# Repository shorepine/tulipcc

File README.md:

# Tulip Creative Computer and AMYboard - portable programmable devices for music, graphics, code and writing

Welcome to the Tulip Creative Computer (Tulip CC) and AMYboard!
 
Tulip is a low power and affordable self-contained portable computer, with a touchscreen display and sound. It's fully programmable - you write code to define your music, games or anything else you can think of. It boots instantaneously into a Python prompt with a lot of built in support for music synthesis, fast graphics and text, hardware MIDI, network access and external sensors. Dive right into making something without distractions or complications. 

The entire system is dedicated to your code, the display and sound, running in real time, on specialized hardware. The hardware and software are fully open source and anyone can [buy one](https://tulip.computer/) or [build one](docs/tulip_build.md). You can use Tulip to make music, code, art, games, or just write. 

[AMYboard](https://amyboard.com) is a headless (no screen) version of Tulip with more audio capability - audio input, modular 10hp and 10vpp audio, S/PDIF digital audio, CV jacks, SD card. It's based on the Tulip code but focused on music synthesis. 

You can now even [run Tulip on the web](https://tulip.computer/run) and [AMYboard on the web](https://amyboard.com/editor) and share your creations with anyone!

Tulip and AMYboard are powered by [MicroPython](https://micropython.org), [AMY](https://github.com/shorepine/amy), and [LVGL](https://lvgl.io). The Tulip hardware runs on the ESP32-S3 chip using the [ESP-IDF](https://github.com/espressif/esp-idf).

 * [**Get a Tulip** from our friends at Makerfabs for only US$59](https://tulip.computer)
 * [**Get an AMYboard** from our friends at Makerfabs for only $29.90](https://amyboard.com)
 * [Just got a Tulip CC? **Check out our getting started guide!**](docs/getting_started.md)
 * [Just got an AMYboard? **Check out our getting started guide!**](docs/amyboard/README.md)
 * [Want to make music with your Tulip? **See our music tutorial**](docs/music.md)
 * [See the full **Tulip API**](docs/tulip_api.md)
 * [**Try out Tulip on the web!**](https://tulip.computer/run/)

 [ **Chat about Tulip on our Discord!**](https://discord.gg/TzBFkUb8pG)

**Check out this video!**

[![Tulip, a musical computer based on Micropython
](https://i.ytimg.com/vi/1lYFjQp7Xrw/maxresdefault.jpg)](https://www.youtube.com/watch?v=1lYFjQp7Xrw "Tulip, a musical computer based on Micropython")

You can use Tulip one of three ways:
 * Tulip is available both as an [off the shelf or DIY hardware project (Tulip CC)](https://tulip.computer/)
 * [Tulip runs on the web](https://tulip.computer/run) with (almost) all the same features. 
 * Tulip can also run as a native app for Mac or Linux (or WSL in Windows) as [Tulip Desktop](docs/tulip_desktop.md)

If you're nervous about getting or building the hardware, [try it out on the web!](https://tulip.computer/run)

The hardware Tulip CC supports:

- 8.5MB of RAM - 2MB is available to MicroPython, and 1.5MB is available for OS memory. The rest is used for the graphics framebuffers (which you can use as storage) and the firmware cache. 
- 32MB flash storage, as a filesystem accesible in Python (24MB left over after OS in ROM)
- An [AMY](https://github.com/shorepine/amy) stereo 120-voice synthesizer engine running locally, or as a wireless controller for an [Alles](https://github.com/shorepine/alles) mesh. Tulip's synth supports additive and subtractive oscillators, an excellent FM synthesis engine, samplers, karplus-strong, high quality analog style filters, a sequencer, and much more. We ship Tulip with a drum machine, voices / patch app, and Juno-6 editor.
- Text frame buffer layer, 128 x 50, with ANSI support for 256 colors, inverse, bold, underline, background color
- Up to 32 sprites on screen, drawn per scanline, with collision detection, from a total of 32KB of bitmap memory (1 byte per pixel)
- A 1024 (+128 overscan) by 600 (+100 overscan) background frame buffer to draw arbitrary bitmaps to, or use as RAM, and which can scroll horizontally / vertically
- WiFi, access http via Python requests or TCP / UDP sockets 
- Adjustable display clock and resolution, defaults to 30 FPS at 1024x600.
- 256 colors
- Can load PNGs from disk to set sprites or background, or generate bitmap data from code
- Built in code and text editor
- Built in BBS chat room and file transfer area called **TULIP ~ WORLD**
- USB keyboard, MIDI and mouse support, including hubs 
- Capactive multi-touch support (mouse on Tulip Desktop and Tulip Web)
- MIDI input and output
- I2C / Grove / Mabee connector, compatible with [many I2C devices like joysticks, keyboard, GPIO, DACs, ADCs, hubs](docs/tulip_api.md#i2c--grove--mabee)
- 575mA power usage @ 5V including display, at medium display brightness, can last for hours on LiPo, 18650s, or USB battery pack 

I've been working on Tulip on and off for years over many hardware iterations and hope that someone out there finds it as fun as I have, either making things with Tulip or working on Tulip itself. I'd love feedback, your own Tulip experiments or pull requests to improve the system.

 * [**Any issues with your Tulip CC? Here's our troubleshooting guide**](docs/troubleshooting.md)
 * [**Learn about our roadmap and find out what we're working on next**](https://github.com/orgs/shorepine/projects/1)
 * [**Build your own Tulip**](docs/tulip_build.md)
 * **[You can read more about the "why" or "how" of Tulip on my website!](https://notes.variogram.com/2024/07/30/tulip-available/)** 

## T-Deck Tulip CC

A **new** small option: get yourself a [T-Deck](https://www.aliexpress.us/item/3256805505920840.html?gatewayAdapt=glo2usa4itemAdapt) and install Tulip CC on it directly! [Check out our T-Deck page for more detail.](tulip/tdeck/README.md)

## Getting started

Once you've [bought a Tulip](https://tulip.computer), [opened Tulip Web](https://tulip.computer/run), [built a Tulip](docs/tulip_build.md) or [installed Tulip Desktop](docs/tulip_desktop.md), you'll see that Tulip boots right into a Python prompt and all interaction with the system happens there. You can make your own Python programs with Tulip's built in editor and execute them, or just experiment on the Tulip REPL prompt in real time.

[**See the full Tulip API**](docs/tulip_api.md) for more details on all the graphics, sound and input functions.

Below are a few getting started tips and small examples. The [full API](docs/tulip_api.md) page has more detail on everything you can do on a Tulip. [**See a more complete getting started page**](docs/getting_started.md) or [**a music making tutorial**](docs/music.md) as well!

```python
# Run a saved Python file. Control-C stops it
cd('ex') # The ex folder has a few examples and graphics in it
execfile("parallax.py")
# If you want to run a Tulip package (folder with other files in it)
run("game")
```

### The Tulip Editor

Tulip ships with a text editor, based on pico/nano. It supports syntax highlighting, search, save/save-as. 

```python
# Opens the Tulip editor to the given filename. 
edit("game.py")
```

### Input and user interface

Tulip supports USB keyboard and mice input as well as touch input. (On Tulip Desktop and Web, mouse clicks act as touch points.) It also comes with UI elements like buttons and sliders to use in your applications, and a way to run mulitple applications as once using callbacks. More in the [full API](docs/tulip_api.md).

```python
(x0, y0, x1, y1, x2, y2) = tulip.touch()
```

### Network

Tulip CC has the capability to connect to a Wi-Fi network, and Python's native requests library will work to access TCP and UDP. We ship a few convenience functions to grab data from URLs as well. More in the [full API](docs/tulip_api.md).

```python
# Join a wifi network (not needed on Tulip Desktop or Web)
tulip.wifi("ssid", "password")

# Get IP address or check if connected
ip_address = tulip.ip() # returns None if not connected

# Save the contents of a URL to disk (needs wifi)
bytes_read = tulip.url_save("https://url", "filename.ext")
```

### Music / sound

Tulip comes with the AMY synthesizer, a very full featured 120-oscillator synth that supports FM, PCM, additive synthesis, partial synthesis, filters, and much more. We also provide a useful "music computer" for scales, chords and progressions. More in the [full API](docs/tulip_api.md) and in the [music tutorial.](docs/music.md) Tulip's version of AMY comes with stereo sound, which you can set per oscillator with the `pan` parameter.

```python
amy.drums() # plays a test song
amy.send(volume=4) # change volume
amy.reset() # stops all music / sounds playing
```
https://user-images.githubusercontent.com/76612/215893940-658144b7-0c6f-42e2-9836-bd271597aab3.mov

### MIDI

Tulip supports MIDI in and out to connect to external music hardware. You can set up a Python callback to respond immediately to any incoming MIDI message. You can also send messages out to MIDI out. More in the [full API](docs/tulip_api.md) and [music tutorial](docs/music.md).

```python
m = tulip.midi_in() # returns bytes of the last MIDI message received
tulip.midi_out((144,60,127)) # sends a note on message
tulip.midi_out(bytes) # Can send bytes or list
```

### Graphics system

The Tulip GPU supports a scrolling background layer, hardware sprites, and a text layer. Much more in the [full API](docs/tulip_api.md).

```python
# Set or get a pixel on the BG
pal_idx = tulip.bg_pixel(x,y)

# Set the contents of a PNG file on the background.
tulip.bg_png(png_filename, x, y)

tulip.bg_scroll(line, x_offset, y_offset, x_speed, y_speed)
```

https://user-images.githubusercontent.com/76612/215895305-7b02ad27-b02a-429a-92ef-f13136e9f9d2.mov

Hardware sprites are supported. They draw over the background and text layer per scanline per frame:

```python
(w, h, bytes) = tulip.sprite_png("filename.png", mem_pos)

...

# Set a sprite x and y position
tulip.sprite_move(12, x, y)
```

https://user-images.githubusercontent.com/76612/215896311-fc0823aa-44bc-4305-85db-a6773db11a98.mov

### Tulip World

Still very much early days, but Tulip supports a native chat and file sharing BBS called **TULIP ~ WORLD** where you can hang out with other Tulip owners. You're able to pull down the latest messages and files and send messages and files yourself. More in the [full API](docs/tulip_api.md).

```python
import world
world.post_message("hello!!") # Sends a message to Tulip World. username required. will prompt if not set
world.upload(filename) # Uploads a file to Tulip World. username required
world.ls() # lists most recent unique filenames/usernames
```

## How to build, compile and help develop Tulip

 * [Get a Tulip!](https://tulip.computer)
 * [Build your own Tulip Creative Computer](docs/tulip_build.md) with FOUR different options.
 * [How to compile and flash Tulip hardware](docs/tulip_flashing.md)
 * [How to run or compile Tulip Desktop](docs/tulip_desktop.md)
 * [The full Tulip API](docs/tulip_api.md)
 * [File any code issues or pull requests!](https://github.com/shorepine/tulipcc/issues)

[ **Chat about Tulip on our Discord!**](https://discord.gg/TzBFkUb8pG)

Two important development guidelines if you'd like to help contribute!

 * Be nice and helpful and don't be afraid to ask questions! We're all doing this for fun and to learn. 
 * Any change or feature must be equivalent across Tulip Desktop and Tulip CC. There are of course limited exceptions to this rule, but please test on hardware before proposing a new feature / change. 

Have fun!

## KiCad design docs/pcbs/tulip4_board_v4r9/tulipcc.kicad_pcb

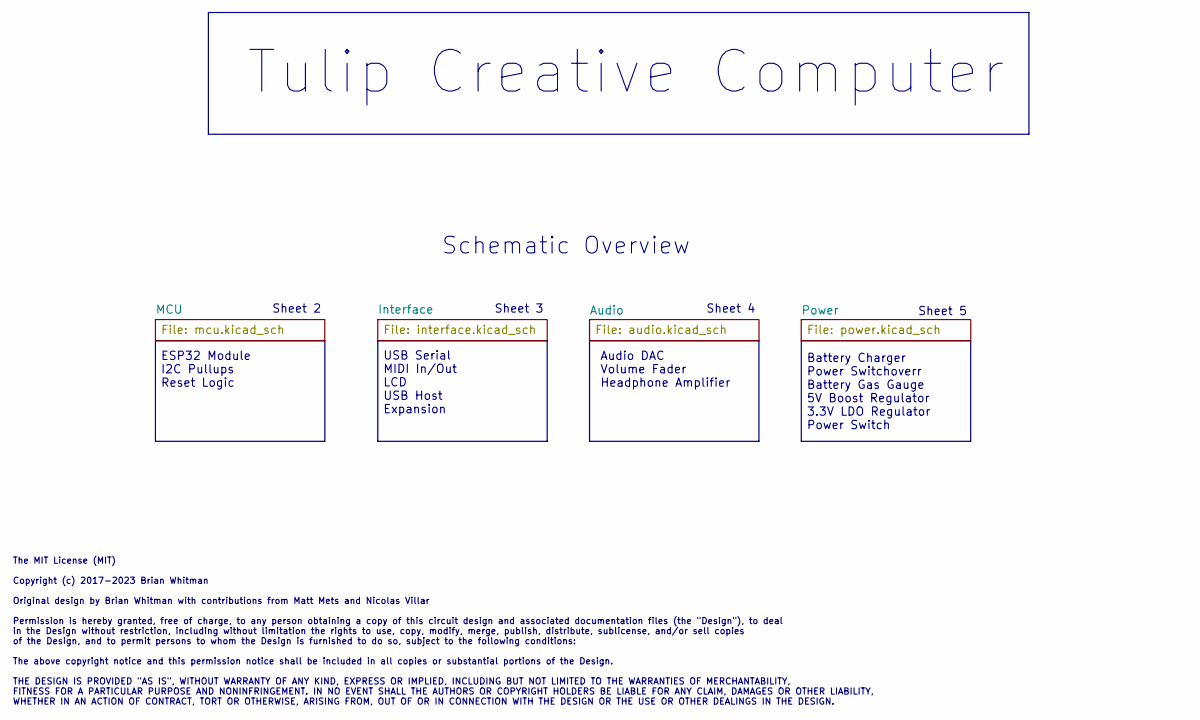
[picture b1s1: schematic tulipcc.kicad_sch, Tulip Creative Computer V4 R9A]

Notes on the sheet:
Schematic Overview
Sheet 2
Sheet 3
Battery Charger Power Switchoverr Battery Gas Gauge 5V Boost Regulator 3.3V LDO Regulator Power Switch
USB Serial MIDI In/Out LCD USB Host Expansion
Tulip Creative Computer
Sheet 4
Sheet 5
The MIT License (MIT) Copyright (c) 2017-2023 Brian Whitman Original design by Brian Whitman with contributions from Matt Mets and Nicolas Villar Permission is hereby granted, free of charge, to any person obtaining a copy of this circuit design and associated documentation files (the "Design"), to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
Audio DAC Volume Fader Headphone Amplifier
ESP32 Module I2C Pullups Reset Logic

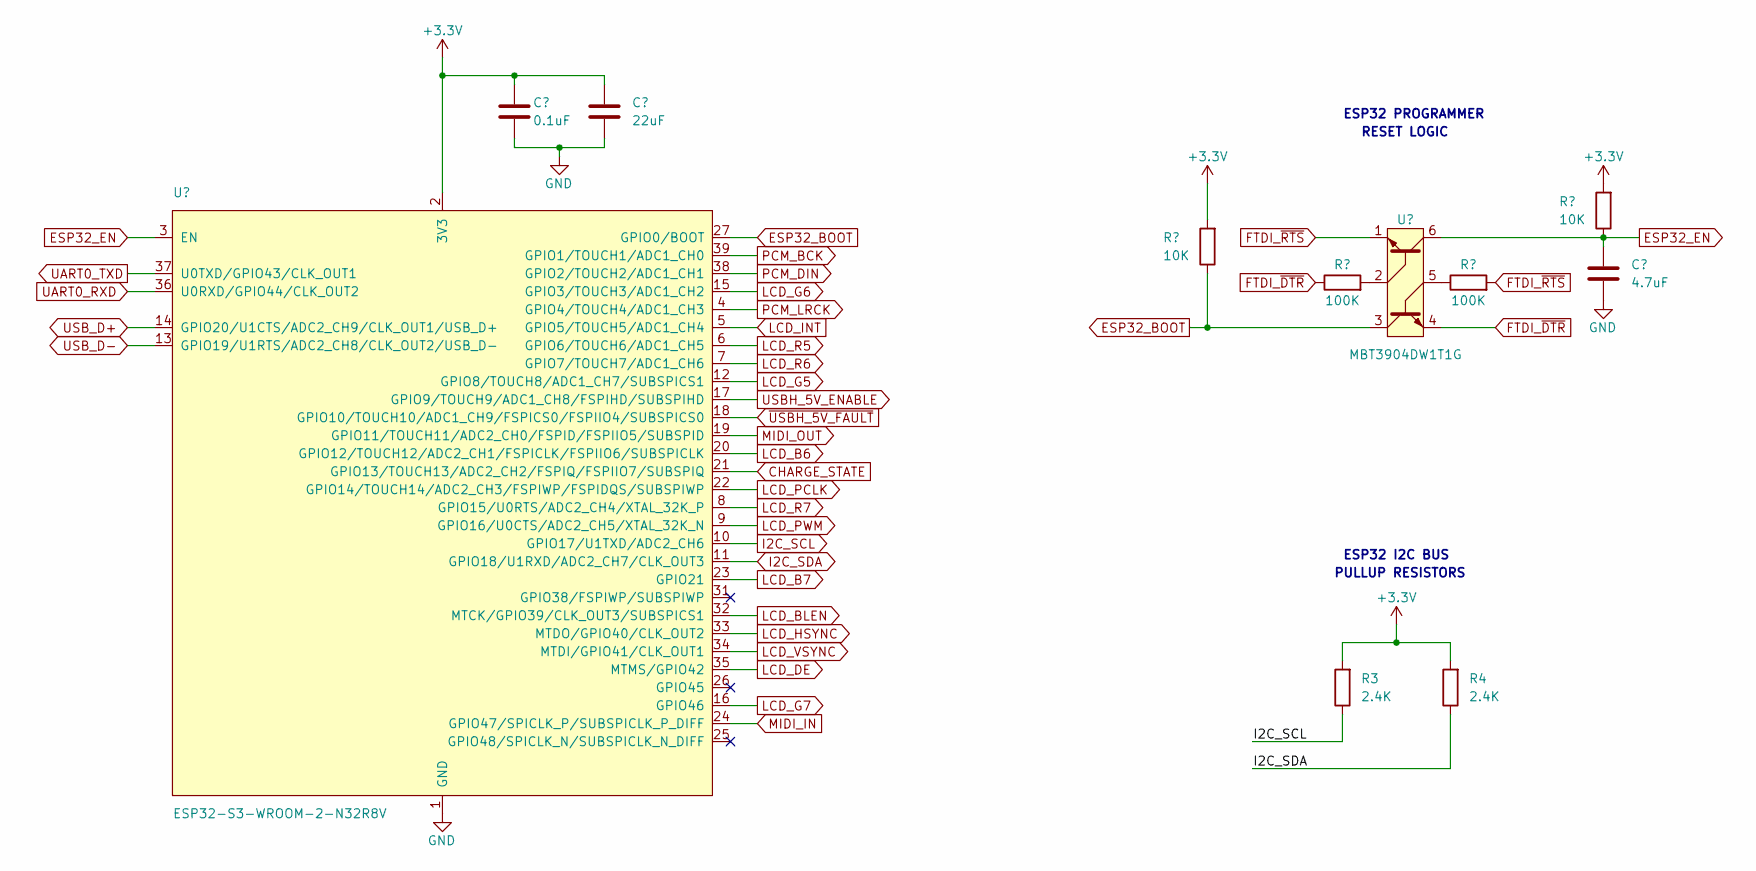
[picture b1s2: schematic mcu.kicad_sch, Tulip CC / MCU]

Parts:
C1: 0.1uF; C_0805_2012; Part # C0805C104K5RAC7411
C2: 22uF; C_1210_3225; Rating 16V; Part # C1210C226M4RAC7210
C3: 4.7uF; C_0805_2012; Part # C0805C475K3RACTU
R1, R2: 10K; R_0805_2012; Part # CR0805-FX-1002ELF
R3, R4: 2.4K; R_0805_2012; Part # CR0805-FX-2401ELF
R5, R6: 100K; R_0805_2012; Part # CR0805-FX-1003ELF
U1: ESP32-S3-WROOM-2-N32R8V; ESP32-S3-WROOM-2; Part # ESP32-S3-WROOM-2-N32R8V
U2: MBT3904DW1T1G; SOT-363_SC-70-6; Part # MBT3904DW1T1G

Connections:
+3.3V: C1.1, C2.2, R1.2, R2.2, R3.2, R4.2, U1.2 (3V3); also elsewhere on the board
CHARGE_STATE: U1.21 (GPIO13/TOUCH13/ADC2_CH2/FSPIQ/FSPIIO7/S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); also elsewhere on the board
ESP32_BOOT: R2.1, U1.27 (GPIO0/BOOT), U2.3
ESP32_EN: C3.1, R1.1, U1.3 (EN), U2.6
FTDI_~DTR: R5.1, U2.4; also elsewhere on the board
FTDI_~RTS: R6.2, U2.1; also elsewhere on the board
GND: C1.2, C2.1, C3.2, U1.1 (GND), U1.40 (GND), U1.41 (GND); also elsewhere on the board
I2C_SCL: R3.1, U1.10 (GPIO17/U1TXD/ADC2_CH6); also elsewhere on the board
I2C_SDA: R4.1, U1.11 (GPIO18/U1RXD/ADC2_CH7/CLK_OUT3); also elsewhere on the board
LCD_B6: U1.20 (GPIO12/TOUCH12/ADC2_CH1/FSPICLK/FSPIIO6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); also elsewhere on the board
LCD_B7: U1.23 (GPIO21); also elsewhere on the board
LCD_BLEN: U1.32 (MTCK/GPIO39/CLK_OUT3/SUBSPICS1); also elsewhere on the board
LCD_DE: U1.35 (MTMS/GPIO42); also elsewhere on the board
LCD_G5: U1.12 (GPIO8/TOUCH8/ADC1_CH7/SUBSPICS1); also elsewhere on the board
LCD_G6: U1.15 (GPIO3/TOUCH3/ADC1_CH2); also elsewhere on the board
LCD_G7: U1.16 (GPIO46); also elsewhere on the board
LCD_HSYNC: U1.33 (MTDO/GPIO40/CLK_OUT2); also elsewhere on the board
LCD_INT: U1.5 (GPIO5/TOUCH5/ADC1_CH4); also elsewhere on the board
LCD_PCLK: U1.22 (GPIO14/TOUCH14/ADC2_CH3/FSPIWP/FSPIDQS/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); also elsewhere on the board
LCD_PWM: U1.9 (GPIO16/U0CTS/ADC2_CH5/XTAL_32K_N); also elsewhere on the board
LCD_R5: U1.6 (GPIO6/TOUCH6/ADC1_CH5); also elsewhere on the board
LCD_R6: U1.7 (GPIO7/TOUCH7/ADC1_CH6); also elsewhere on the board
LCD_R7: U1.8 (GPIO15/U0RTS/ADC2_CH4/XTAL_32K_P); also elsewhere on the board
LCD_VSYNC: U1.34 (MTDI/GPIO41/CLK_OUT1); also elsewhere on the board
MIDI_IN: U1.24 (GPIO47/SPICLK_P/SUBSPICLK_P_DIFF); also elsewhere on the board
MIDI_OUT: U1.19 (GPIO11/TOUCH11/ADC2_CH0/FSPID/FSPIIO5/S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); also elsewhere on the board
unnamed: R5.2, U2.2
unnamed: R6.1, U2.5
PCM_BCK: U1.39 (GPIO1/TOUCH1/ADC1_CH0); also elsewhere on the board
PCM_DIN: U1.38 (GPIO2/TOUCH2/ADC1_CH1); also elsewhere on the board
PCM_LRCK: U1.4 (GPIO4/TOUCH4/ADC1_CH3); also elsewhere on the board
UART0_RXD: U1.36 (U0RXD/GPIO44/CLK_OUT2); also elsewhere on the board
UART0_TXD: U1.37 (U0TXD/GPIO43/CLK_OUT1); also elsewhere on the board
USBH_5V_ENABLE: U1.17 (GPIO9/TOUCH9/ADC1_CH8/FSPIHD/SUBSPIHD); also elsewhere on the board
USB_D+: U1.14 (GPIO20/U1CTS/ADC2_CH9/CLK_OUT1/USB_D+); also elsewhere on the board
USB_D-: U1.13 (GPIO19/U1RTS/ADC2_CH8/CLK_OUT2/USB_D-); also elsewhere on the board
~USBH_5V_FAULT: U1.18 (GPIO10/TOUCH10/ADC1_CH9/FSPICS0/FSPIIO4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); also elsewhere on the board

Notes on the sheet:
PULLUP RESISTORS
RESET LOGIC
ESP32 I2C BUS
ESP32 PROGRAMMER

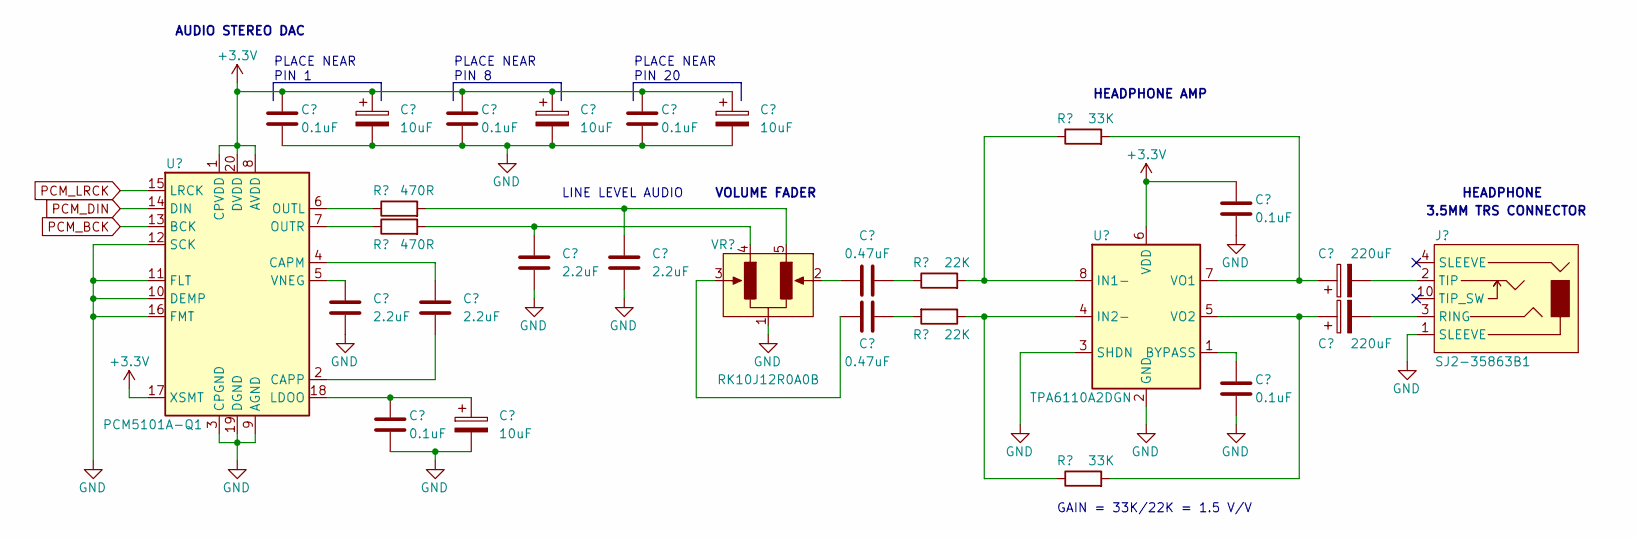
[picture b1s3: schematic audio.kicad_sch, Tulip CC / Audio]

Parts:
C11, C13, C15, C17, C26, C27: 0.1uF; C_0805_2012; Part # C0805C104K5RAC7411
C12, C14, C16, C28: 10uF; CAP_WE_865060340001; Rating 16V; Part # 865060340001
C18, C19, C22, C23: 2.2uF; C_0805_2012; Part # C0805C225K3RACTU
C20, C24: 0.47uF; C_0805_2012; Part # C0805C474K3RACTU
C21, C25: 220uF; CAP_WE_865060345007; Rating 16V; Part # 865060345007
J7: SJ2-35863B1; CON_CUI_SJ2-35863B1-SMT; Part # SJ2-35863B1-SMT-TR
R21, R26: 33K; R_0805_2012; Part # CR0805-FX-3002ELF
R22, R23: 470R; R_0805_2012; Part # CR0805-FX-4700ELF
R24, R25: 22K; R_0805_2012; Part # CR0805-FX-2202ELF
U8: PCM5101A-Q1; TSSOP-20_4.4x6.5mm_P0.65mm; Part # PCM5101AQPWRQ1
U9: TPA6110A2DGN; HVSSOP-8-1EP_3x3mm_P0.65mm_EP1.57x1.89mm; Part # TPA6110A2DGNR
VR1: RK10J12R0A0B; ALPS_RK10J12R0A0B; Part # RK10J12R0A0B

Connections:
+3.3V: C11.1, C12.1, C13.1, C14.1, C15.1, C16.1, C17.1, U8.1 (CPVDD), U8.8 (AVDD), U8.17 (XSMT), U8.20 (DVDD), U9.6 (VDD); also elsewhere on the board
GND: C11.2, C12.2, C13.2, C14.2, C15.2, C16.2, C17.2, C18.2, C19.2, C22.2, C26.2, C27.2, C28.2, J7.1 (SLEEVE), U8.3 (CPGND), U8.9 (AGND), U8.10 (DEMP), U8.11 (FLT), U8.12 (SCK), U8.16 (FMT), U8.19 (DGND), U9.2 (GND), U9.3 (SHDN), U9.9 (GND), VR1.1; also elsewhere on the board
unnamed: C18.1, R23.2, VR1.4
unnamed: C19.1, R22.2, VR1.5
unnamed: C20.1, R24.1
unnamed: C20.2, VR1.2
unnamed: C24.1, R25.2
unnamed: C24.2, VR1.3
unnamed: C25.2, J7.3 (RING)
unnamed: C21.2, J7.2 (TIP)
unnamed: C23.1, U8.4 (CAPM)
unnamed: C23.2, U8.2 (CAPP)
unnamed: C27.1, C28.1, U8.18 (LDOO)
unnamed: R22.1, U8.6 (OUTL)
unnamed: R23.1, U8.7 (OUTR)
unnamed: C22.1, U8.5 (VNEG)
unnamed: C26.1, U9.1 (BYPASS)
unnamed: R21.1, R24.2, U9.8 (IN1-)
unnamed: R25.1, R26.1, U9.4 (IN2-)
unnamed: C21.1, R21.2, U9.7 (VO1)
unnamed: C25.1, R26.2, U9.5 (VO2)
PCM_BCK: U8.13 (BCK); also elsewhere on the board
PCM_DIN: U8.14 (DIN); also elsewhere on the board
PCM_LRCK: U8.15 (LRCK); also elsewhere on the board

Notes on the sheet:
GAIN = 33K/22K = 1.5 V/V
3.5MM TRS CONNECTOR
HEADPHONE AMP
VOLUME FADER
PLACE NEAR PIN 20
PLACE NEAR PIN 1
HEADPHONE
PLACE NEAR PIN 8
LINE LEVEL AUDIO
AUDIO STEREO DAC

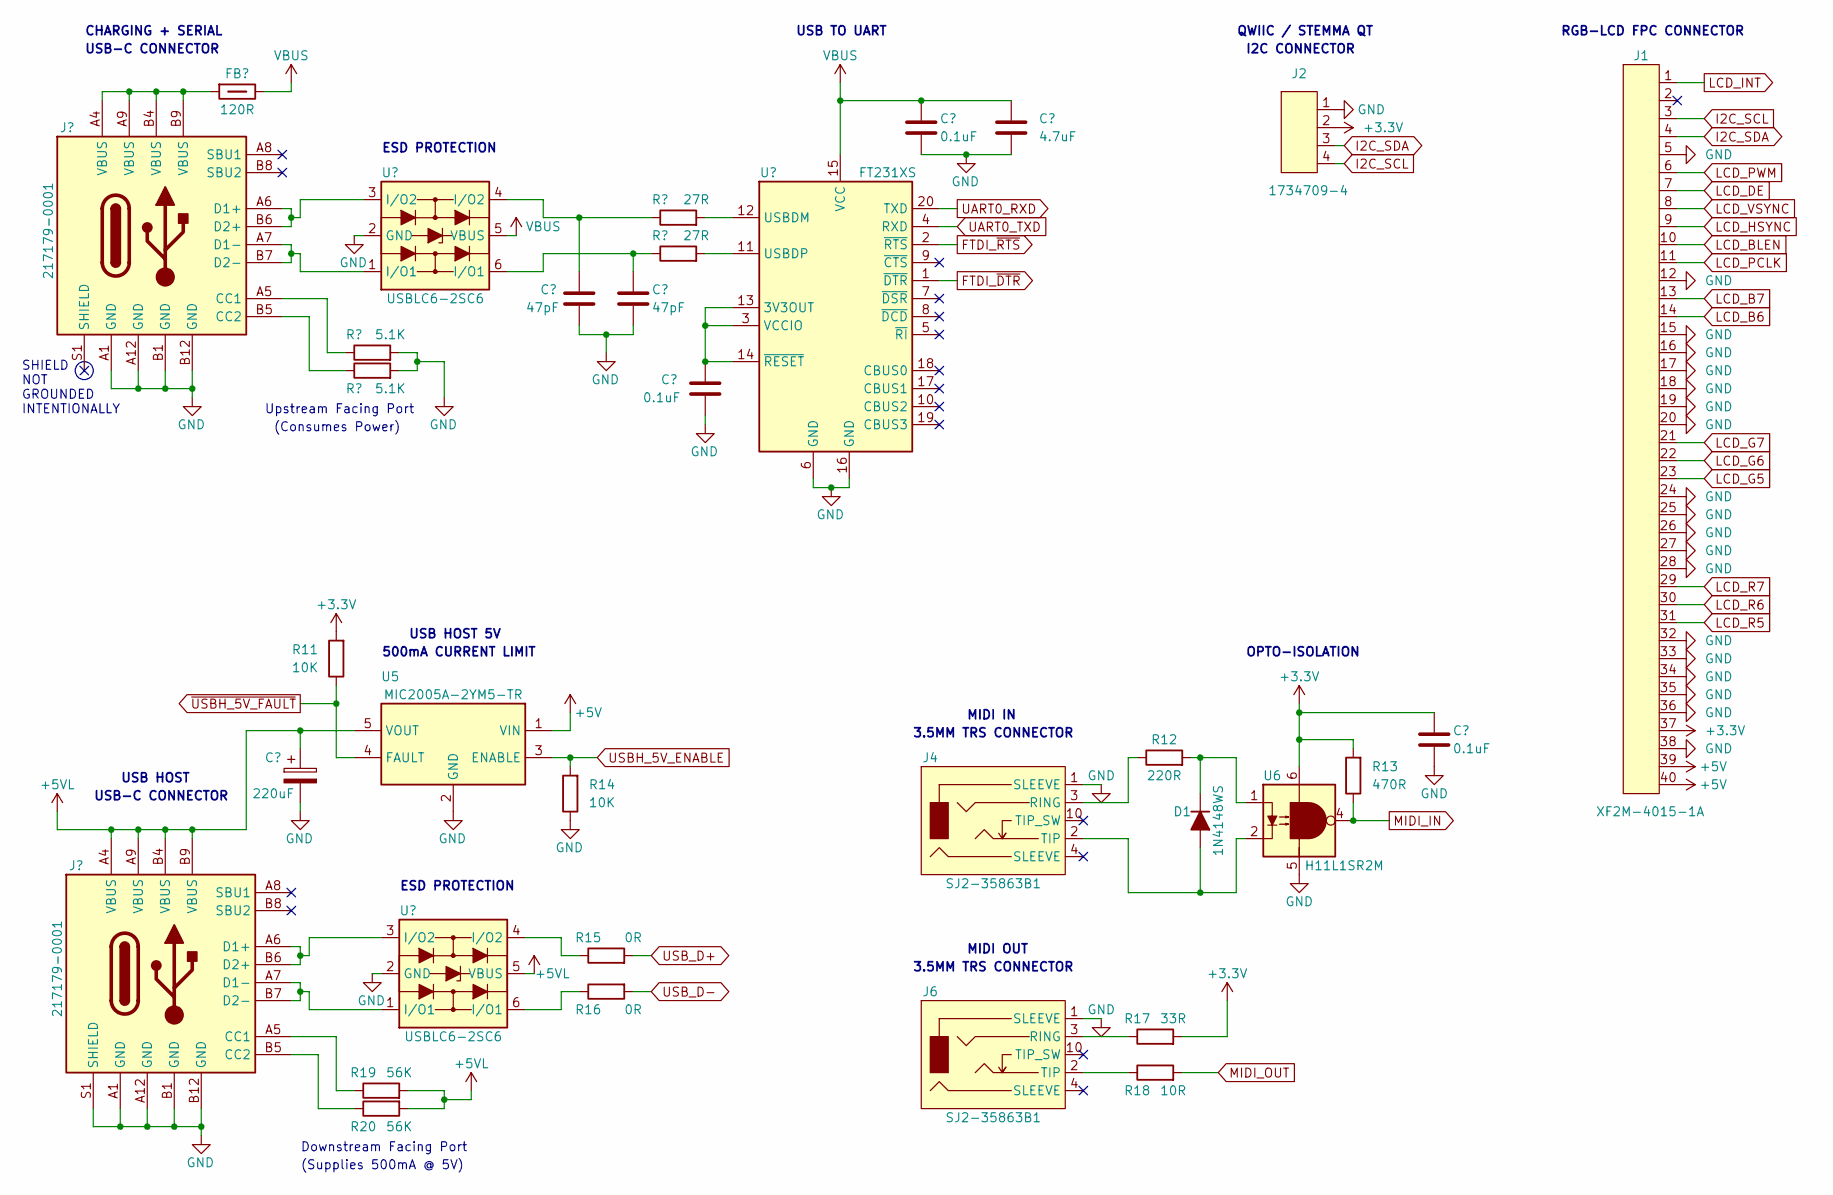
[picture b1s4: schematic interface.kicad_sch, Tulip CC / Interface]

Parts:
C4, C8, C9: 0.1uF; C_0805_2012; Part # C0805C104K5RAC7411
C5: 4.7uF; C_0805_2012; Part # C0805C475K3RACTU
C6, C7: 47pF; C_0805_2012; Part # C0805C470K5RACTU
C10: 220uF; CAP_WE_865060345007; Rating 16V; Part # 865060345007
D1: 1N4148WS; D_SOD-323; Part # 1N4148WS-G3-08
FB1: 120R; FB_0805_2012; Part # BLM21PG121SN1D
J1: XF2M-4015-1A; OMRON_XF2M-4015-1A; Part # XF2M-4015-1A
J2: 1734709-4; TE_1734709-4; Part # 1734709-4
J3, J5: 217179-0001; USB-C_Molex_217179-0001; Part # 217179-0001
J4, J6: SJ2-35863B1; CON_CUI_SJ2-35863B1-SMT; Part # SJ2-35863B1-SMT-TR
R7, R8: 27R; R_0805_2012; Part # CR0805-FX-27R0ELF
R9, R10: 5.1K; R_0805_2012; Part # CR0805-FX-5101ELF
R11, R14: 10K; R_0805_2012; Part # CR0805-FX-1002ELF
R12: 220R; R_0805_2012; Part # CR0805-FX-2200ELF
R13: 470R; R_0805_2012; Part # CR0805-FX-4703ELF
R15, R16: 0R; R_0805_2012; Part # CR0805-J/-000ELF
R17: 33R; R_0805_2012; Part # CR0805-FX-3002ELF
R18: 10R; R_0805_2012; Part # CR0805-FX-10R0ELF
R19, R20: 56K; R_0805_2012; Part # CR0805-FX-5602ELF
U3, U7: USBLC6-2SC6; SOT-23-6; Part # USBLC6-2SC6
U4: FT231XS; SSOP-20_3.9x8.7mm_P0.635mm; Part # FT231XS-R
U5: MIC2005A-2YM5-TR; SOT-23-5; Part # MIC2005A-2YM5-TR
U6: H11L1SR2M; PDIP6-SMD; Part # H11L1SR2M

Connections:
+3.3V: C9.1, J1.37, J2.2, R11.2, R13.2, R17.2, U6.6; also elsewhere on the board
+5V: J1.39, J1.40, U5.1 (VIN); also elsewhere on the board
+5VL: C10.1, J5.A4 (VBUS), J5.A9 (VBUS), J5.B4 (VBUS), J5.B9 (VBUS), R19.2, R20.2, U5.5 (VOUT), U7.5 (VBUS)
FTDI_~DTR: U4.1 (~DTR); also elsewhere on the board
FTDI_~RTS: U4.2 (~RTS); also elsewhere on the board
GND: C4.2, C5.2, C6.2, C7.2, C8.2, C9.2, C10.2, J1.5, J1.12, J1.15, J1.16, J1.17, J1.18, J1.19, J1.20, J1.24, J1.25, J1.26, J1.27, J1.28, J1.32, J1.33, J1.34, J1.35, J1.36, J1.38, J2.1, J3.A1 (GND), J3.A12 (GND), J3.B1 (GND), J3.B12 (GND), J4.1 (SLEEVE), J5.A1 (GND), J5.A12 (GND), J5.B1 (GND), J5.B12 (GND), J5.S1 (SHIELD), J6.1 (SLEEVE), R9.2, R10.2, R14.1, U3.2 (GND), U4.6 (GND), U4.16 (GND), U5.2 (GND), U6.5, U7.2 (GND); also elsewhere on the board
I2C_SCL: J1.3, J2.4; also elsewhere on the board
I2C_SDA: J1.4, J2.3; also elsewhere on the board
LCD_B6: J1.14; also elsewhere on the board
LCD_B7: J1.13; also elsewhere on the board
LCD_BLEN: J1.10; also elsewhere on the board
LCD_DE: J1.7; also elsewhere on the board
LCD_G5: J1.23; also elsewhere on the board
LCD_G6: J1.22; also elsewhere on the board
LCD_G7: J1.21; also elsewhere on the board
LCD_HSYNC: J1.9; also elsewhere on the board
LCD_INT: J1.1; also elsewhere on the board
LCD_PCLK: J1.11; also elsewhere on the board
LCD_PWM: J1.6; also elsewhere on the board
LCD_R5: J1.31; also elsewhere on the board
LCD_R6: J1.30; also elsewhere on the board
LCD_R7: J1.29; also elsewhere on the board
LCD_VSYNC: J1.8; also elsewhere on the board
MIDI_IN: R13.1, U6.4; also elsewhere on the board
MIDI_OUT: R18.2; also elsewhere on the board
unnamed: C6.1, R7.1, U3.4 (I/O2)
unnamed: C7.1, R8.1, U3.6 (I/O1)
unnamed: D1.2 (A), J4.2 (TIP), U6.2
unnamed: D1.1 (K), R12.2, U6.1
unnamed: FB1.1, J3.A4 (VBUS), J3.A9 (VBUS), J3.B4 (VBUS), J3.B9 (VBUS)
unnamed: J3.A5 (CC1), R9.1
unnamed: J3.B5 (CC2), R10.1
unnamed: J3.A6 (D1+), J3.B6 (D2+), U3.3 (I/O2)
unnamed: J3.A7 (D1-), J3.B7 (D2-), U3.1 (I/O1)
unnamed: J4.3 (RING), R12.1
unnamed: J5.A5 (CC1), R19.1
unnamed: J5.B5 (CC2), R20.1
unnamed: J5.A6 (D1+), J5.B6 (D2+), U7.3 (I/O2)
unnamed: J5.A7 (D1-), J5.B7 (D2-), U7.1 (I/O1)
unnamed: J6.3 (RING), R17.1
unnamed: J6.2 (TIP), R18.1
unnamed: R15.1, U7.4 (I/O2)
unnamed: R16.1, U7.6 (I/O1)
unnamed: C8.1, U4.3 (VCCIO), U4.13 (3V3OUT), U4.14 (~RESET)
UART0_RXD: U4.20 (TXD); also elsewhere on the board
UART0_TXD: U4.4 (RXD); also elsewhere on the board
USBH_5V_ENABLE: R14.2, U5.3 (ENABLE); also elsewhere on the board
USB_D+: R15.2; also elsewhere on the board
USB_D-: R16.2; also elsewhere on the board
VBUS: C4.1, C5.1, FB1.2, U3.5 (VBUS), U4.15 (VCC); also elsewhere on the board
~USBH_5V_FAULT: R11.1, U5.4 (FAULT); also elsewhere on the board

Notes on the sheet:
USB TO UART
3.5MM TRS CONNECTOR
500mA CURRENT LIMIT
OPTO-ISOLATION
MIDI IN
USB-C CONNECTOR
USB HOST 5V
ESD PROTECTION
USB HOST
SHIELD NOT GROUNDED INTENTIONALLY
I2C CONNECTOR
RGB-LCD FPC CONNECTOR
MIDI OUT
Upstream Facing Port
QWIIC / STEMMA QT
(Consumes Power)
Downstream Facing Port
CHARGING + SERIAL
(Supplies 500mA @ 5V)

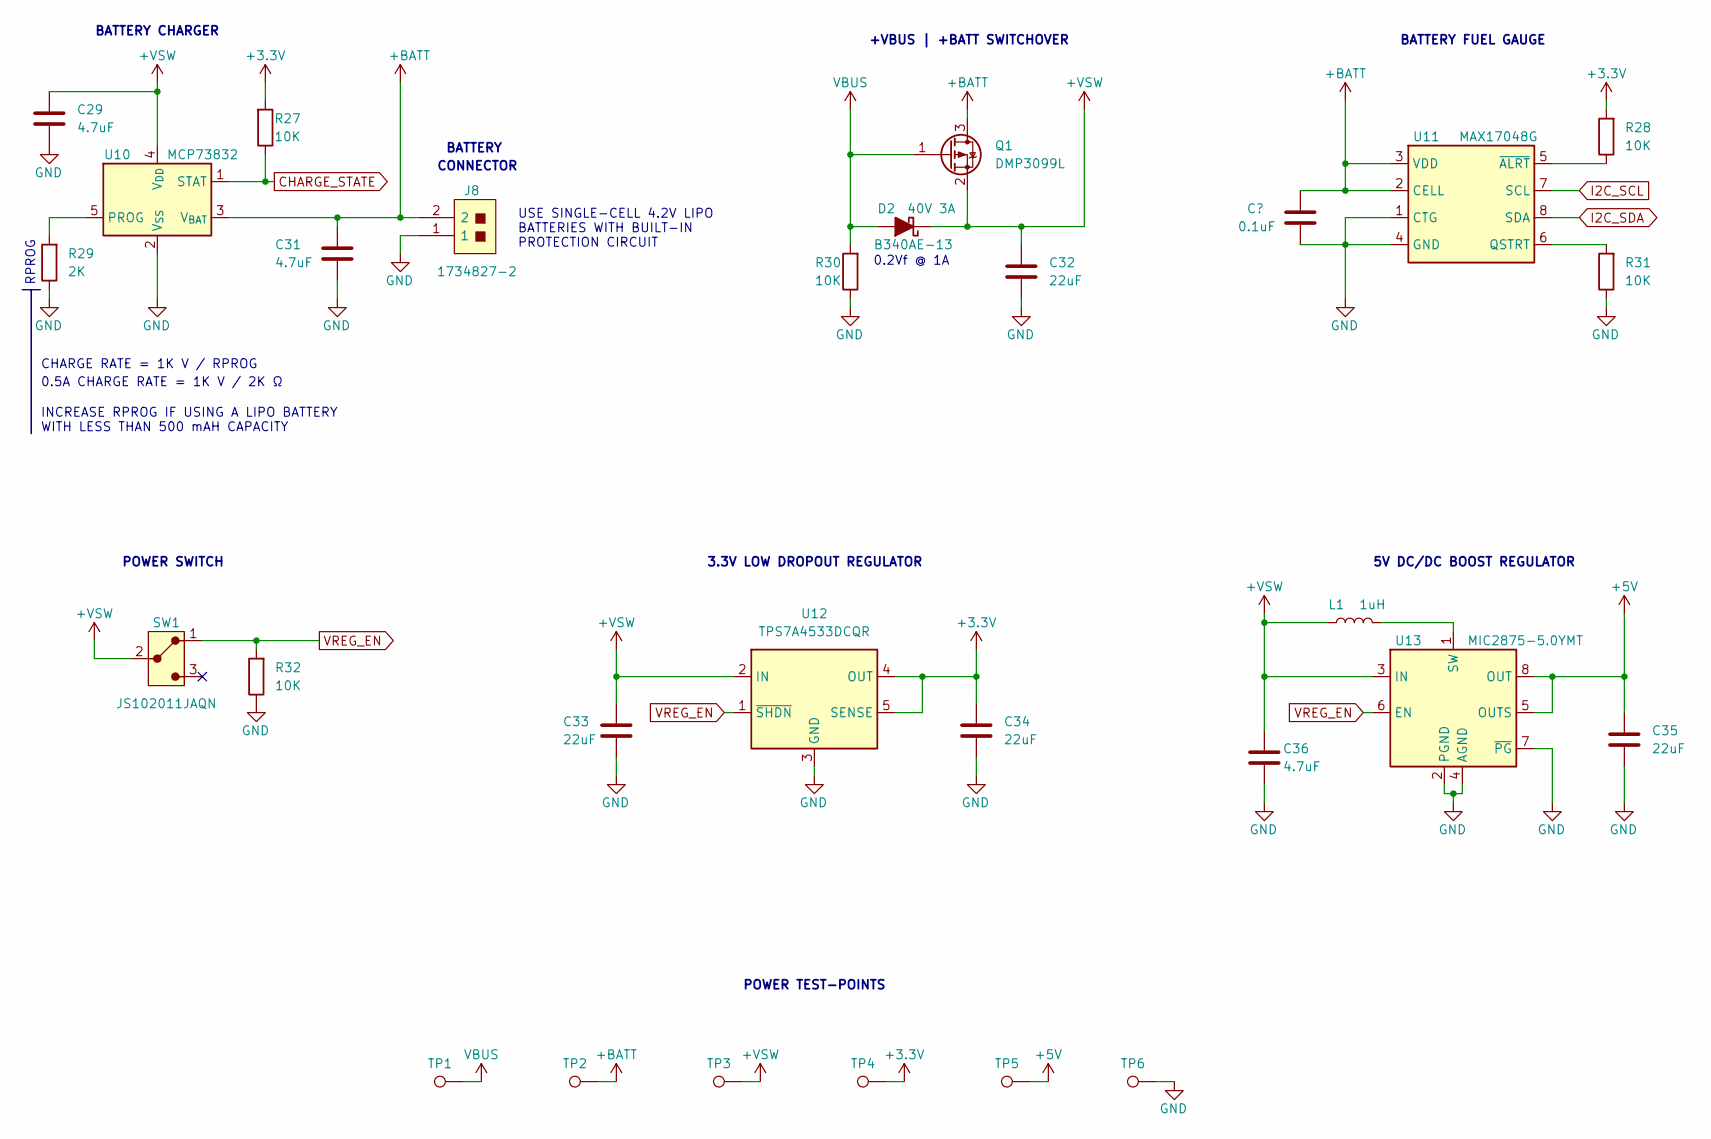
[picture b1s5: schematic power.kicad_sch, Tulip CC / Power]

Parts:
C29, C31, C36: 4.7uF; C_0805_2012; Part # C0805C475K3RACTU
C30: 0.1uF; C_0805_2012; Part # C0805C104K5RAC7411
C32, C33, C34, C35: 22uF; C_1210_3225; Rating 16V; Part # C1210C226M4RAC7210
D2: B340AE-13; D_SMA; Rating 40V 3A; Part # B340AE-13
J8: 1734827-2; TE_17348272; Part # 1734827-2
L1: 1uH; IND_VD_IFSC-1515AH-01; Rating 3.8A 25mR; Part # IFSC1515AHER1R0M01
Q1: DMP3099L; SOT-23-3; Part # DMP3099L-13
R27, R28, R30, R31, R32: 10K; R_0805_2012; Part # CR0805-FX-1002ELF
R29: 2K; R_0805_2012; Part # CR0805-FX-2001ELF
SW1: JS102011JAQN; CK_JS102011JAQN; Part # JS102011JAQN
TP1, TP2, TP3, TP4, TP5, TP6: PCB Test Point; TEST_POINT; Part # N/A
U10: MCP73832; SOT-23-5; Part # MCP73832T-2ACI/OT
U11: MAX17048G; TDFN-8-1EP_2x2mm_P0.5mm_EP0.8x1.2mm; Part # MAX17048G+T10
U12: TPS7A4533DCQR; SOT-223-6; Part # TPS7A4533DCQR
U13: MIC2875-5.0YMT; UDFN-8-1EP_2x2mm_P0.5mm_EP0.7x1.3mm_1; Part # MIC2875-5.0YMT

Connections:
+3.3V: C34.2, R27.2, R28.2, TP4.1, U12.4 (OUT), U12.5 (SENSE); also elsewhere on the board
+5V: C35.2, TP5.1, U13.5 (OUTS), U13.8 (OUT); also elsewhere on the board
+BATT: C30.1, C31.1, J8.2, Q1.3 (D), TP2.1, U10.3 (V_{BAT}), U11.2 (CELL), U11.3 (VDD)
+VSW: C29.1, C32.1, C33.2, C36.1, D2.1 (K), L1.1, Q1.2 (S), SW1.2, TP3.1, U10.4 (V_{DD}), U12.2 (IN), U13.3 (IN)
CHARGE_STATE: R27.1, U10.1 (STAT); also elsewhere on the board
GND: C29.2, C30.2, C31.2, C32.2, C33.1, C34.1, C35.1, C36.2, J8.1, R29.1, R30.1, R31.1, R32.1, TP6.1, U10.2 (V_{SS}), U11.1 (CTG), U11.4 (GND), U11.9 (GND), U12.3 (GND), U12.6 (GND), U13.2 (PGND), U13.4 (AGND), U13.7 (~PG), U13.9 (AGND); also elsewhere on the board
I2C_SCL: U11.7 (SCL); also elsewhere on the board
I2C_SDA: U11.8 (SDA); also elsewhere on the board
unnamed: R29.2, U10.5 (PROG)
unnamed: R31.2, U11.6 (QSTRT)
unnamed: R28.1, U11.5 (~ALRT)
unnamed: L1.2, U13.1 (SW)
VBUS: D2.2 (A), Q1.1 (G), R30.2, TP1.1; also elsewhere on the board
VREG_EN: R32.2, SW1.1, U12.1 (~SHDN), U13.6 (EN)

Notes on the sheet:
BATTERY
0.2Vf @ 1A
3.3V LOW DROPOUT REGULATOR
RPROG
BATTERY CHARGER
+VBUS | +BATT SWITCHOVER
POWER TEST-POINTS
BATTERY FUEL GAUGE
INCREASE RPROG IF USING A LIPO BATTERY WITH LESS THAN 500 mAH CAPACITY
USE SINGLE-CELL 4.2V LIPO BATTERIES WITH BUILT-IN PROTECTION CIRCUIT
POWER SWITCH
CONNECTOR
0.5A CHARGE RATE = 1K V / 2K Ω
5V DC/DC BOOST REGULATOR
CHARGE RATE = 1K V / RPROG

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
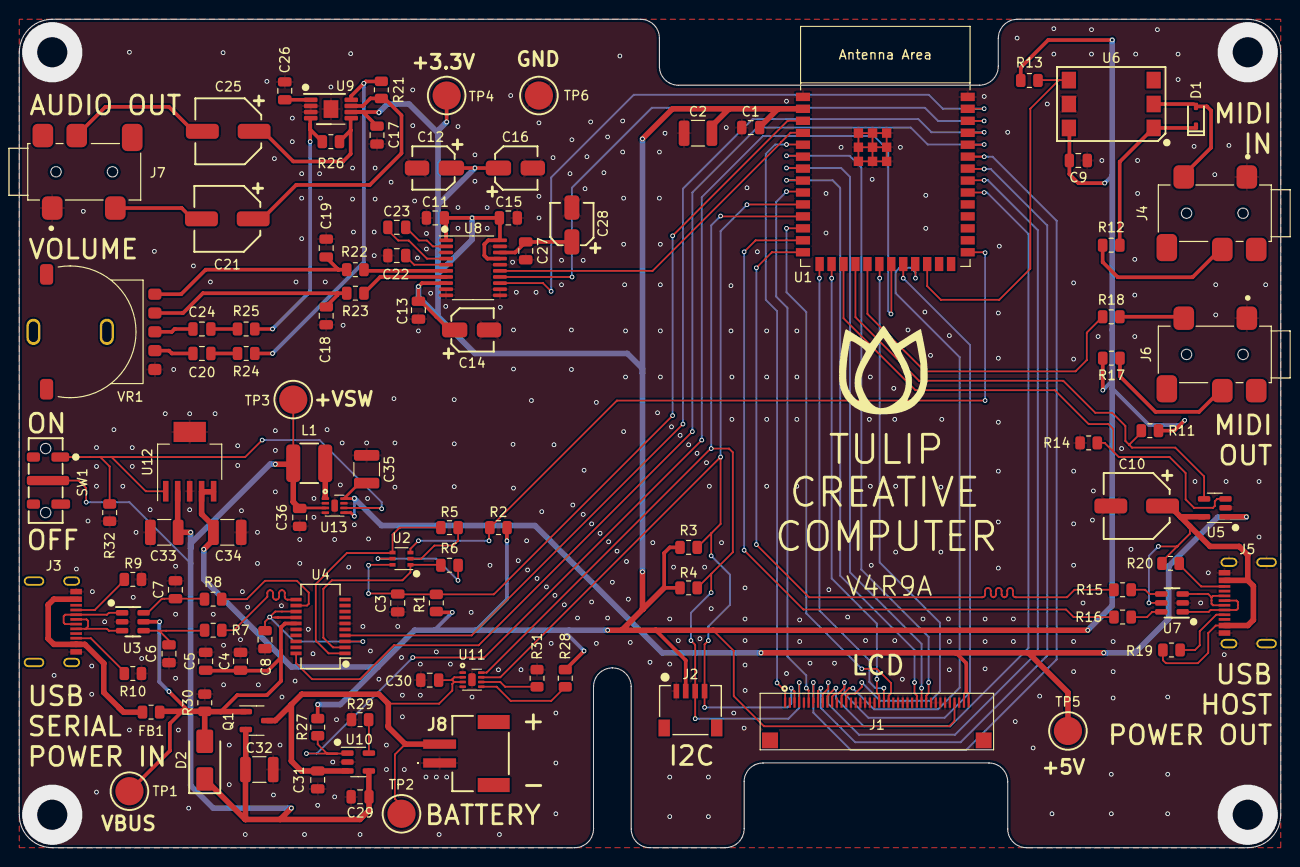
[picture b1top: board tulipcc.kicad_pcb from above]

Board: 2 copper layers, 134.0 x 88.0 mm, 102 parts (0 on the bottom side), 87 nets.

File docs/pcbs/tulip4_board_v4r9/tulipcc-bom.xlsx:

Bill of Materials
Tulip Creative Computer V4R9A
Item | Qty | Reference(s) | Value | Manufacturer | Part # | Supplier 1 | Supplier 1 # | Supplier 2 | Supplier 2 #
1 | 11 | C1, C4, C8, C9, C11, C13, C15, C17, C26, C27, C30 | 0.1uF | Kemet | C0805C104K5RAC7411 | Mouser | 80-C0805C104K5RACLR | DigiKey | 399-C0805C104K5RAC7800CT-ND
2 | 5 | C2, C32, C33, C34, C35 | 22uF | Kemet | C1210C226M4RAC7210 | Mouser | 80-C1210C226M4RACLR | DigiKey | 399-C1210C226M4RAC7210CT-ND
3 | 5 | C3, C5, C29, C31, C36 | 4.7uF | Kemet | C0805C475K3RACTU | Mouser | 80-C0805C475K3RACTU | DigiKey | 399-C0805C475K3RAC7800CT-ND
4 | 2 | C6, C7 | 47pF | Kemet | C0805C470K5RACTU | Mouser | 80-C0805C470K5RACTU | DigiKey | 399-C0805C470K5RAC7800CT-ND
5 | 3 | C10, C21, C25 | 220uF | WE | 865060345007 | Mouser | 710-865060345007 | DigiKey | 732-8524-1-ND
6 | 4 | C12, C14, C16, C28 | 10uF | WE | 865060340001 | Mouser | 710-865060340001 | DigiKey | 732-8518-1-ND
7 | 4 | C18, C19, C22, C23 | 2.2uF | Kemet | C0805C225K3RACTU | Mouser | 80-C0805C225K3R | DigiKey | 399-11941-1-ND
8 | 2 | C20, C24 | 0.47uF | Kemet | C0805C474K3RACTU | Mouser | 80-C0805C474K3R | DigiKey | 399-C0805C474K3NAC7800CT-ND
9 | 1 | D1 | 1N4148WS | Vishay | 1N4148WS-G3-08 | Mouser | 78-1N4148WS-G3-08 | DigiKey | 1N4148WS-G3-08GICT-ND
10 | 1 | D2 | B340AE-13 | Diodes Inc | B340AE-13 | Mouser | 621-B340AE-13 | DigiKey | B340AE-13DICT-ND
11 | 1 | FB1 | 120R | Murata | BLM21PG121SN1D | Mouser | 81-BLM18SG121TN1D | DigiKey | 490-BLM21PG121BH1DCT-ND
12 | 1 | J1 | XF2M-4015-1A | Omron | XF2M-4015-1A | Mouser | 653-XF2M-4015-1A | DigiKey | OR729CT-ND
13 | 1 | J2 | 1734709-4 | TE | 1734709-4 | Mouser | 571-1734709-4 | DigiKey | A99957CT-ND
14 | 2 | J3, J5 | 217179-0001 | Molex | 217179-0001 | Mouser | 538-217179-0001 | DigiKey | 900-2171790001CT-ND
15 | 3 | J4, J6, J7 | SJ2-35863B1 | CUI | SJ2-35863B1-SMT-TR | Mouser | 595-TPA6110A2DGNR | DigiKey | CP-SJ2-35863B1-SMT-CT-ND
16 | 1 | J8 | 1734827-2 | TE | 1734827-2 | Mouser | 571-1734827-2 | DigiKey | 455-S2B-PH-SM4-TBCT-ND
17 | 1 | L1 | 1uH | Vishay Dale | IFSC1515AHER1R0M01 | Mouser | 70-IFSC1515AHER1R0M0 | DigiKey | 541-1403-1-ND
18 | 1 | Q1 | DMP3099L | Diodes Inc | DMP3099L-13 | Mouser | 621-DMP3099L-13 | DigiKey | DMP3099L-13DICT-ND
19 | 9 | R1, R2, R11, R14, R27, R28, R30, R31, R32 | 10K | Bourns | CR0805-FX-1002ELF | Mouser | 652-CR0805FX-1002ELF | DigiKey | CR0805-FX-1002ELFCT-ND
20 | 2 | R3, R4 | 2.4K | Bourns | CR0805-FX-2401ELF | Mouser | 652-CR0805FX-2401ELF | DigiKey | CR0805-FX-2401ELFCT-ND
21 | 2 | R5, R6 | 100K | Bourns | CR0805-FX-1003ELF | Mouser | 652-CR0805FX-1003ELF | DigiKey | CR0805-FX-1003ELFCT-ND
22 | 2 | R7, R8 | 27R | Bourns | CR0805-FX-27R0ELF | Mouser | 652-CR0805FX-27R0ELF | DigiKey | 118-CMP0603AFX-27R0ELFCT-ND
23 | 2 | R9, R10 | 5.1K | Bourns | CR0805-FX-5101ELF | Mouser | 652-CR0805FX-5101ELF | DigiKey | CR0805-FX-5101ELFCT-ND
24 | 1 | R12 | 220R | Bourns | CR0805-FX-2200ELF | Mouser | 652-CR0805FX-2200ELF | DigiKey | CR0805-FX-2200ELFCT-ND
25 | 3 | R13, R22, R23 | 470R | Bourns | CR0805-FX-4700ELF | Mouser | 652-CR0805FX-4700ELF | DigiKey | CR0805-FX-4700ELFCT-ND
26 | 2 | R15, R16 | 0R | Bourns | CR0805-J/-000ELF | Mouser | 652-CR0805-J/-000ELF | DigiKey | CR0805-J/-000ELFCT-ND
27 | 1 | R17 | 33R | Bourns | CR0805-FX-3002ELF | Mouser | 652-CR0805FX-33R0ELF | DigiKey | 118-CR0805-FX-3002ELFCT-ND
28 | 1 | R18 | 10R | Bourns | CR0805-FX-10R0ELF | Mouser | 652-CR0805FX-10R0ELF | DigiKey | 118-CR0805-FX-10R0ELFCT-ND
29 | 2 | R19, R20 | 56K | Bourns | CR0805-FX-5602ELF | Mouser | 652-CR0805FX-5602ELF | DigiKey | 118-CR0805-FX-5602ELFCT-ND
30 | 2 | R21, R26 | 33K | Bourns | CR0805-FX-3302ELF | Mouser | 652-CR0805FX-3302ELF | DigiKey | CR0805-FX-3302ELFCT-ND
31 | 2 | R24, R25 | 22K | Bourns | CR0805-FX-2202ELF | Mouser | 652-CR0805-FX2202ELF | DigiKey | CR0805-FX-2202ELFCT-ND
32 | 1 | R29 | 2K | Bourns | CR0805-FX-2001ELF | Mouser | 652-CR0805FX-2001ELF | DigiKey | CR0805-FX-2001ELFCT-ND
33 | 1 | SW1 | JS102011JAQN | C&K | JS102011JAQN | Mouser | 611-JS102011JAQN | DigiKey | CKN10720CT-ND
34 | 1 | U1 | ESP32-S3-WROOM-2-N32R8V | Espressif | ESP32-S3-WROOM-2-N32R8V | Mouser | 356-ESP3S3WRM2N32R8V | DigiKey | 1965-ESP32-S3-WROOM-2-N32R8VCT-ND
35 | 1 | U2 | MBT3904DW1T1G | Onsemi | MBT3904DW1T1G | Mouser | 863-MBT3904DW1T1G | DigiKey | MBT3904DW1T1GOSCT-ND
36 | 2 | U3, U7 | USBLC6-2SC6 | ST | USBLC6-2SC6 | Mouser | 511-USBLC6-2SC6 | DigiKey | 497-5235-1-ND
37 | 1 | U4 | FT231XS | FTDI | FT231XS-R | Mouser | 895-FT231XS-R | DigiKey | 768-1129-1-ND
38 | 1 | U5 | MIC2005A-2YM5-TR | Microchip | MIC2005A-2YM5-TR | Mouser | 998-MIC2005A-2YM5TR | DigiKey | 576-3464-1-ND
39 | 1 | U6 | H11L1SR2M | Onsemi | H11L1SR2M | Mouser | 512-H11L1SR2M | DigiKey | H11L1SR2MCT-ND
40 | 1 | U8 | PCM5101A-Q1 | TI | PCM5101AQPWRQ1 | Mouser | 595-PCM5101AQPWRQ1 | DigiKey | 296-37276-1-ND
41 | 1 | U9 | TPA6110A2DGN | TI | TPA6110A2DGNR | Mouser | 595-TPA6110A2DGNR | DigiKey | 296-31976-1-ND
42 | 1 | U10 | MCP73832 | Microchip | MCP73832T-2ACI/OT | Mouser | 579-MCP73832T-2ACIOT | DigiKey | MCP73832T-2ACI/OTCT-ND
43 | 1 | U11 | MAX17048G | Analog Devices | MAX17048G+T10 | Mouser | 700-MAX17048G+T10 | DigiKey | MAX17048G+T10CT-ND
44 | 1 | U12 | TPS7A4533DCQR | TI | TPS7A4533DCQR | Mouser | 595-TPS7A4533DCQR | DigiKey | 296-37002-1-ND
45 | 1 | U13 | MIC2875-5.0YMT | Microchip | MIC2875-5.0YMT | Mouser | 998-MIC2875-50YMTT5 | Microchip | MIC2875-5.0YMT-TR
46 | 1 | VR1 | RK10J12R0A0B | Alps | RK10J12R0A0B | Mouser | 688-RK10J12R0A0B
